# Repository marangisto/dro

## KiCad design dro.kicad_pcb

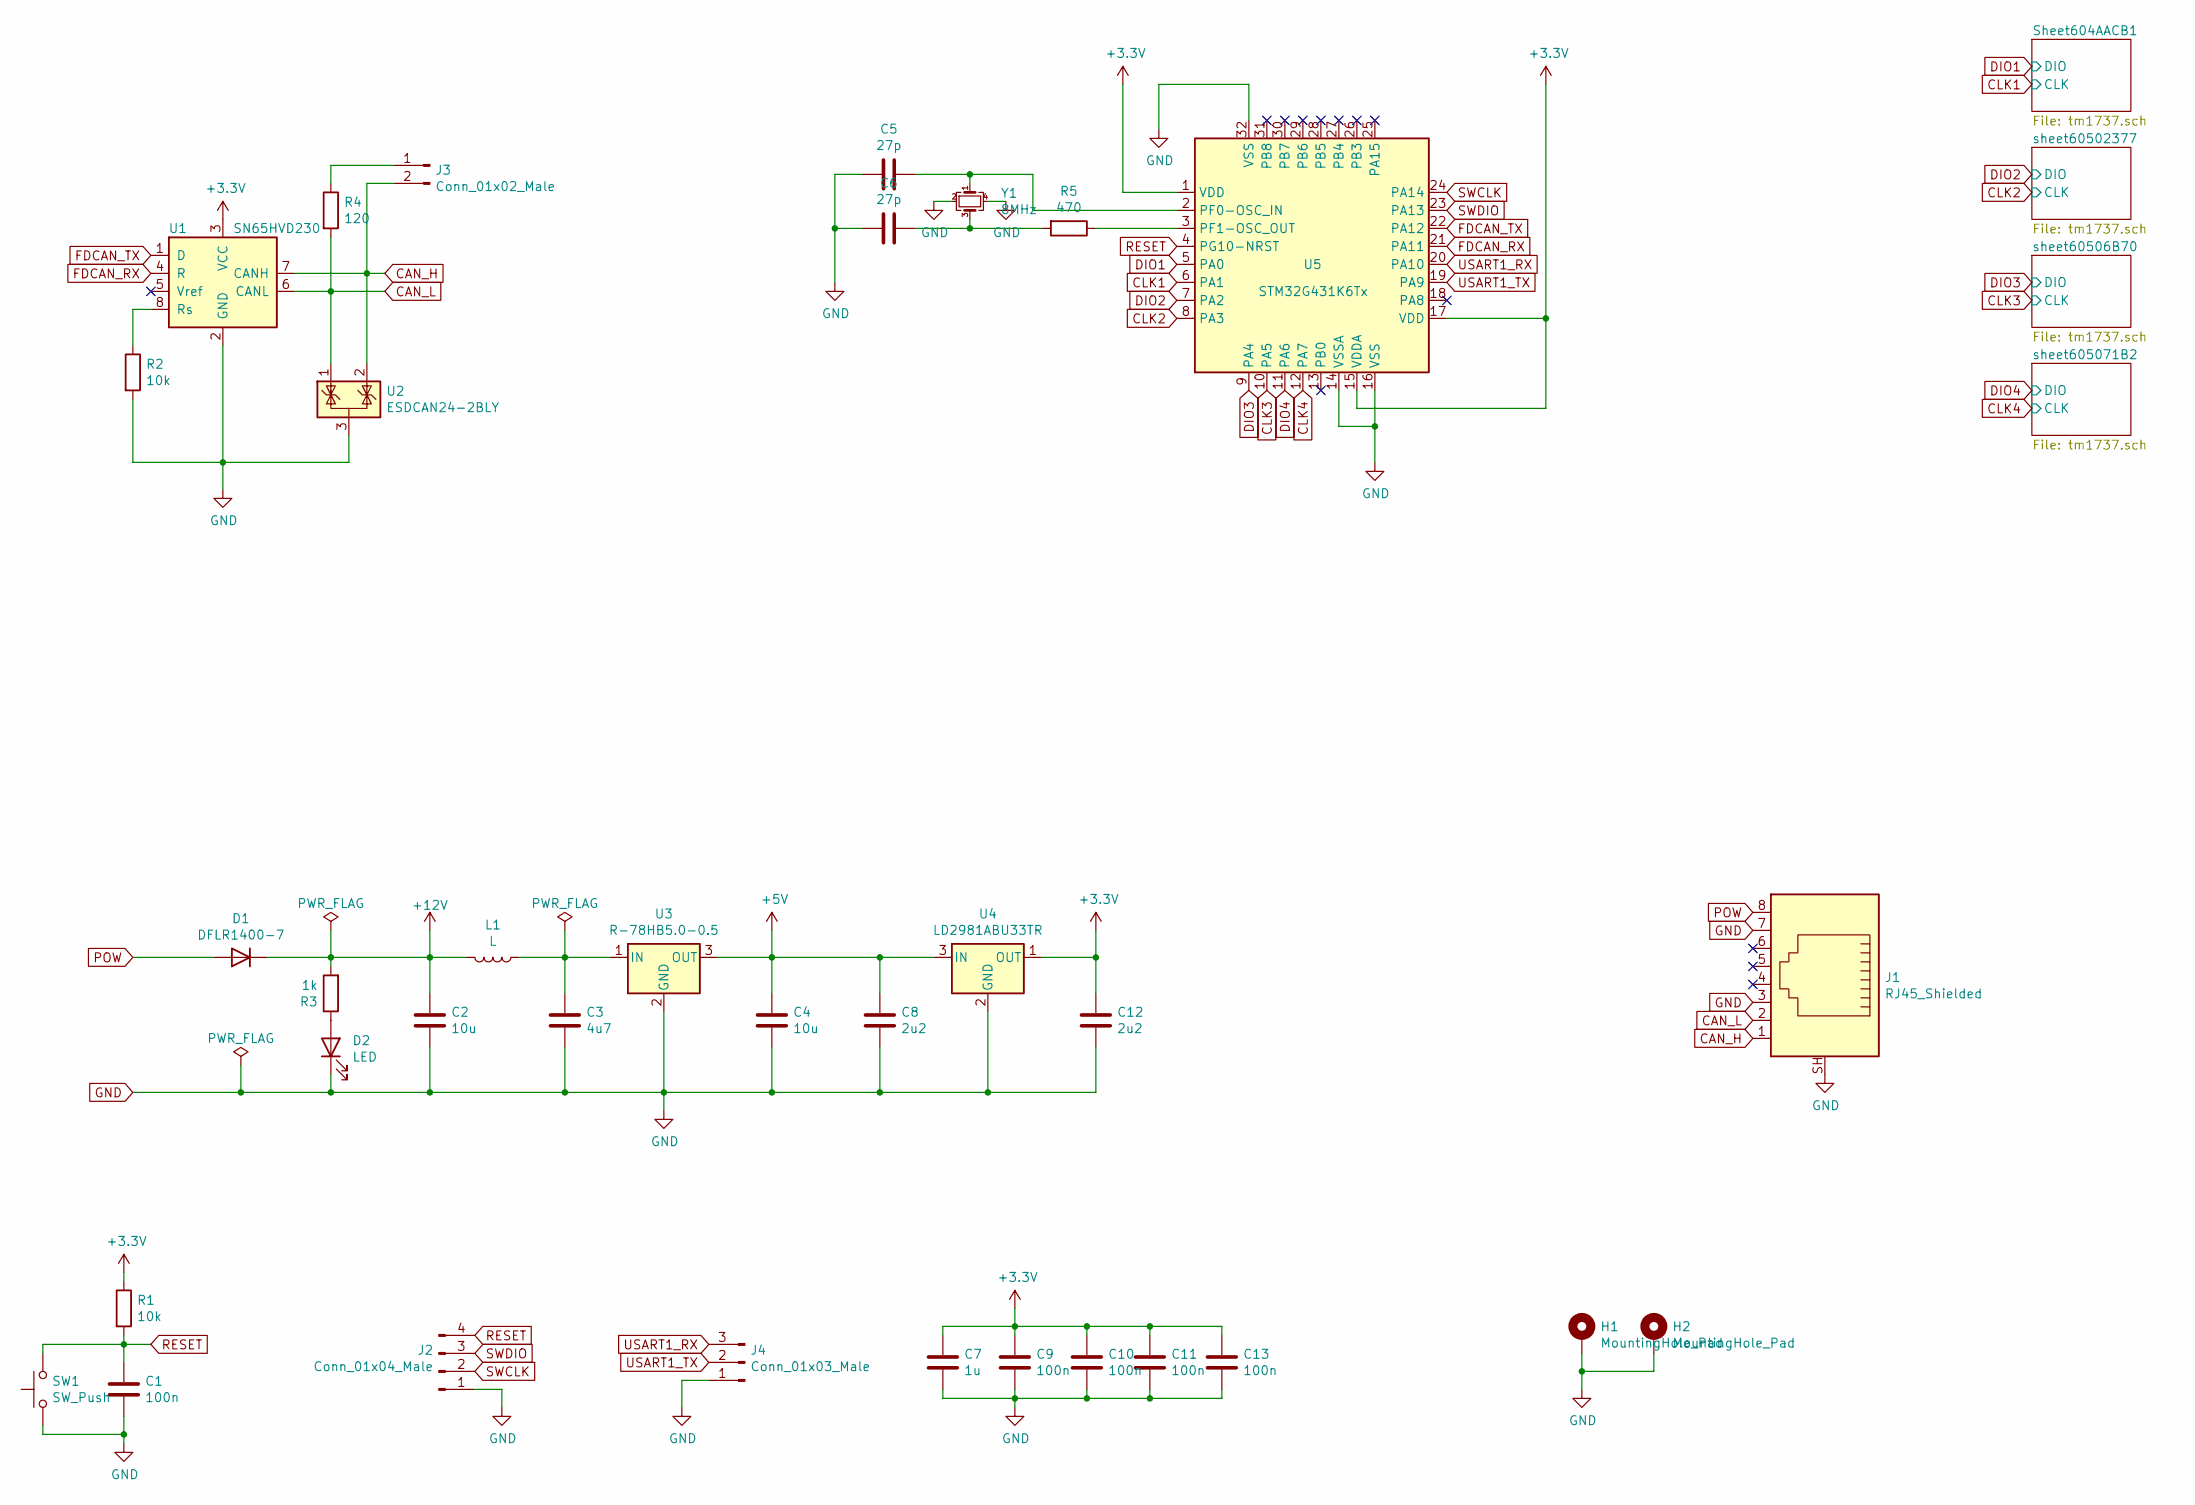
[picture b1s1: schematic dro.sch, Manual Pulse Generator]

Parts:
C1, C9, C10, C11, C13: 100n; C_0603_1608Metric
C2, C4: 10u; C_1206_3216Metric
C3: 4u7; C_1206_3216Metric
C5, C6: 27p; C_0603_1608Metric
C7: 1u; C_0603_1608Metric
C8, C12: 2u2; C_0805_2012Metric
D1: DFLR1400-7; D_PowerDI-123
D2: LED; LED_0603_1608Metric_Castellated
H1, H2: MountingHole_Pad; MountingHole_3.2mm_M3_Pad_Via
J1: RJ45_Shielded; RJ45-Wurth-615008142621
J2: Conn_01x04_Male; PinHeader_1x04_P2.54mm_Vertical
J3: Conn_01x02_Male; PinHeader_1x02_P2.54mm_Vertical
J4: Conn_01x03_Male; PinHeader_1x03_P2.54mm_Vertical
L1: L; L_Coilcraft_LPS5030
R1, R2: 10k; R_0603_1608Metric
R3: 1k; R_0603_1608Metric
R4: 120; R_0603_1608Metric
R5: 470; R_0603_1608Metric
SW1: SW_Push; SW_PUSH_6mm
U1: SN65HVD230; SOIC-8_3.9x4.9mm_P1.27mm
U2: ESDCAN24-2BLY; SOT-23
U3: R-78HB5.0-0.5; Converter_DCDC_RECOM_R-78HB-0.5_THT
U4: LD2981ABU33TR; SOT-89-3
U5: STM32G431K6Tx; LQFP-32_7x7mm_P0.8mm
Y1: 8MHz; Crystal_SMD_5032-4Pin_5.0x3.2mm

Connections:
+3V3: C7.1, C9.1, C10.1, C11.1, C12.1, C13.1, R1.1, U1.3 (VCC), U4.1 (OUT), U5.1 (VDD), U5.15 (VDDA), U5.17 (VDD); also elsewhere on the board
+5V: C4.1, C8.1, U3.3 (OUT), U4.3 (IN); also elsewhere on the board
+12V: C2.1, D1.1 (K), L1.2, R3.2
CAN_H: J1.1, J3.2, U1.7 (CANH), U2.2 (K)
CAN_L: J1.2, R4.2, U1.6 (CANL), U2.1 (K)
CLK1: U5.6 (PA1); also elsewhere on the board
CLK2: U5.8 (PA3); also elsewhere on the board
CLK3: U5.10 (PA5); also elsewhere on the board
CLK4: U5.12 (PA7); also elsewhere on the board
DIO1: U5.5 (PA0); also elsewhere on the board
DIO2: U5.7 (PA2); also elsewhere on the board
DIO3: U5.9 (PA4); also elsewhere on the board
DIO4: U5.11 (PA6); also elsewhere on the board
FDCAN_RX: U1.4 (R), U5.21 (PA11)
FDCAN_TX: U1.1 (D), U5.22 (PA12)
GND: C1.2, C2.2, C3.2, C4.2, C5.2, C6.2, C7.2, C8.2, C9.2, C10.2, C11.2, C12.2, C13.2, D2.1 (K), H1.1, H2.1, J1.3, J1.7, J1.SH, J2.1, J4.1, R2.2, SW1.1, U1.2 (GND), U2.3 (A), U3.2 (GND), U4.2 (GND), U5.14 (VSSA), U5.16 (VSS), U5.32 (VSS), Y1.2, Y1.4; also elsewhere on the board
unnamed: C3.1, L1.1, U3.1 (IN)
unnamed: C5.1, U5.2 (PF0-OSC_IN), Y1.1
unnamed: C6.1, R5.2, Y1.3
unnamed: D2.2 (A), R3.1
unnamed: J3.1, R4.1
unnamed: R2.1, U1.8 (Rs)
unnamed: R5.1, U5.3 (PF1-OSC_OUT)
POW: D1.2 (A), J1.8
RESET: C1.1, J2.4, R1.2, SW1.2, U5.4 (PG10-NRST)
SWCLK: J2.2, U5.24 (PA14)
SWDIO: J2.3, U5.23 (PA13)
USART1_RX: J4.3, U5.20 (PA10)
USART1_TX: J4.2, U5.19 (PA9)

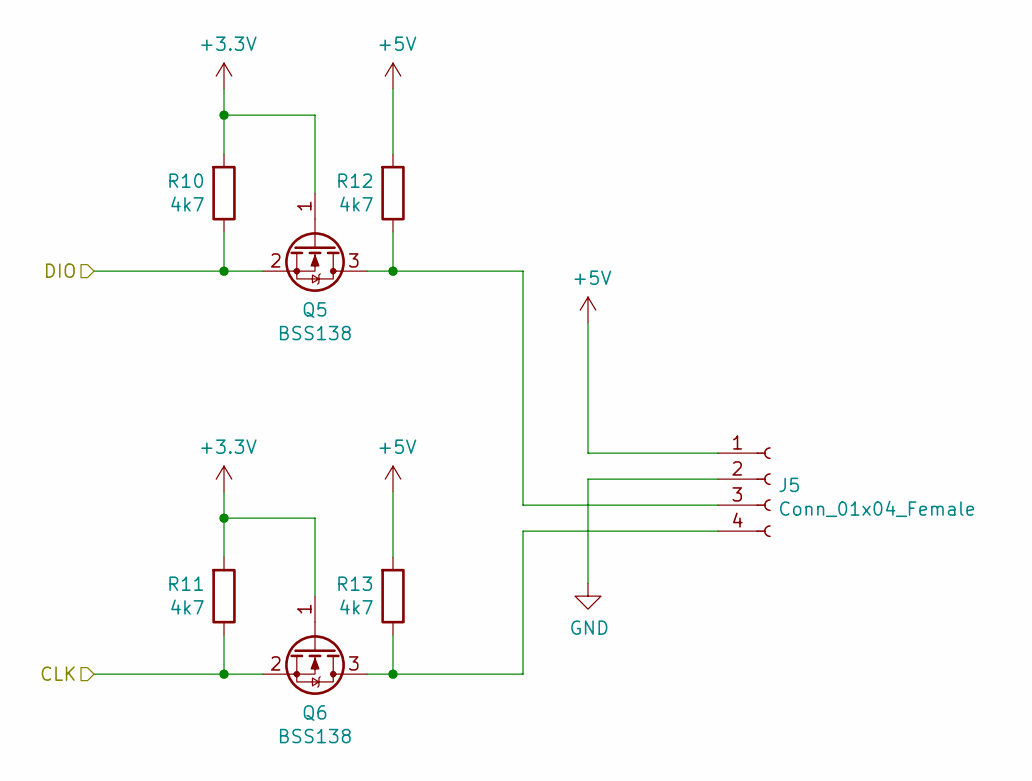
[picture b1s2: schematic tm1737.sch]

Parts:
J5: Conn_01x04_Female; PinSocket_1x04_P2.54mm_Vertical
Q5, Q6: BSS138; SOT-23
R10, R11, R12, R13: 4k7; R_0603_1608Metric

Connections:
+3V3: Q5.1 (G), Q6.1 (G), R10.2, R11.2; also elsewhere on the board
+5V: J5.1, R12.2, R13.2; also elsewhere on the board
CLK1: Q6.2 (S), R11.1; also elsewhere on the board
DIO1: Q5.2 (S), R10.1; also elsewhere on the board
GND: J5.2; also elsewhere on the board
unnamed: J5.3, Q5.3 (D), R12.1
unnamed: J5.4, Q6.3 (D), R13.1

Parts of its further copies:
J6, J7, J8: Conn_01x04_Female; PinSocket_1x04_P2.54mm_Vertical
Q7, Q8, Q9, Q10, Q11, Q12: BSS138; SOT-23
R14, R15, R16, R17, R18, R19, R20, R21, R22, R23, R24, R25: 4k7; R_0603_1608Metric

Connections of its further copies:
+3V3: Q7.1 (G), Q8.1 (G), Q9.1 (G), Q10.1 (G), Q11.1 (G), Q12.1 (G), R14.2, R15.2, R18.2, R19.2, R22.2, R23.2; also elsewhere on the board
+5V: J6.1, J7.1, J8.1, R16.2, R17.2, R20.2, R21.2, R24.2, R25.2; also elsewhere on the board
CLK2: Q8.2 (S), R15.1; also elsewhere on the board
CLK3: Q10.2 (S), R19.1; also elsewhere on the board
CLK4: Q12.2 (S), R23.1; also elsewhere on the board
DIO2: Q7.2 (S), R14.1; also elsewhere on the board
DIO3: Q9.2 (S), R18.1; also elsewhere on the board
DIO4: Q11.2 (S), R22.1; also elsewhere on the board
GND: J6.2, J7.2, J8.2; also elsewhere on the board
unnamed: J6.3, Q7.3 (D), R16.1
unnamed: J6.4, Q8.3 (D), R17.1
unnamed: J7.3, Q9.3 (D), R20.1
unnamed: J7.4, Q10.3 (D), R21.1
unnamed: J8.3, Q11.3 (D), R24.1
unnamed: J8.4, Q12.3 (D), R25.1

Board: 2 copper layers, 62 parts (0 on the bottom side), 37 nets, no tracks yet.

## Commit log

2021-01-30 Initial project.
2021-02-14 Initial design.
2021-03-03 Removed unused declarations.
